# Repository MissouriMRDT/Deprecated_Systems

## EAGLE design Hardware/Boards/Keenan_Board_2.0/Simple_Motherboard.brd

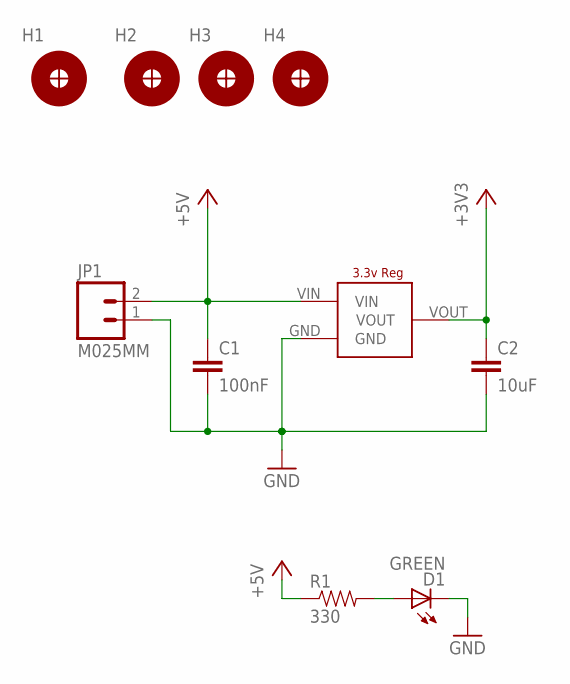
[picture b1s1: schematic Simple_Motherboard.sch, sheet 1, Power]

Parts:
C1: 100nF; 1206
C2: 10uF; 1206
D1: GREEN; LED-1206
H1, H2, H3, H4: H_MNTHOLE_#4
JP1: M025MM; SCREWTERMINAL-5MM-2
R1: 330; 1206
U$1: LD1117; LD1117SOT-223

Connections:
+3V3: C2.1, U$1.VOUT; also elsewhere on the board
+5V: C1.1, JP1.2, R1.1, U$1.VIN; also elsewhere on the board
GND: C1.2, C2.2, D1.C, JP1.1, U$1.GND; also elsewhere on the board
unnamed: D1.A, R1.2

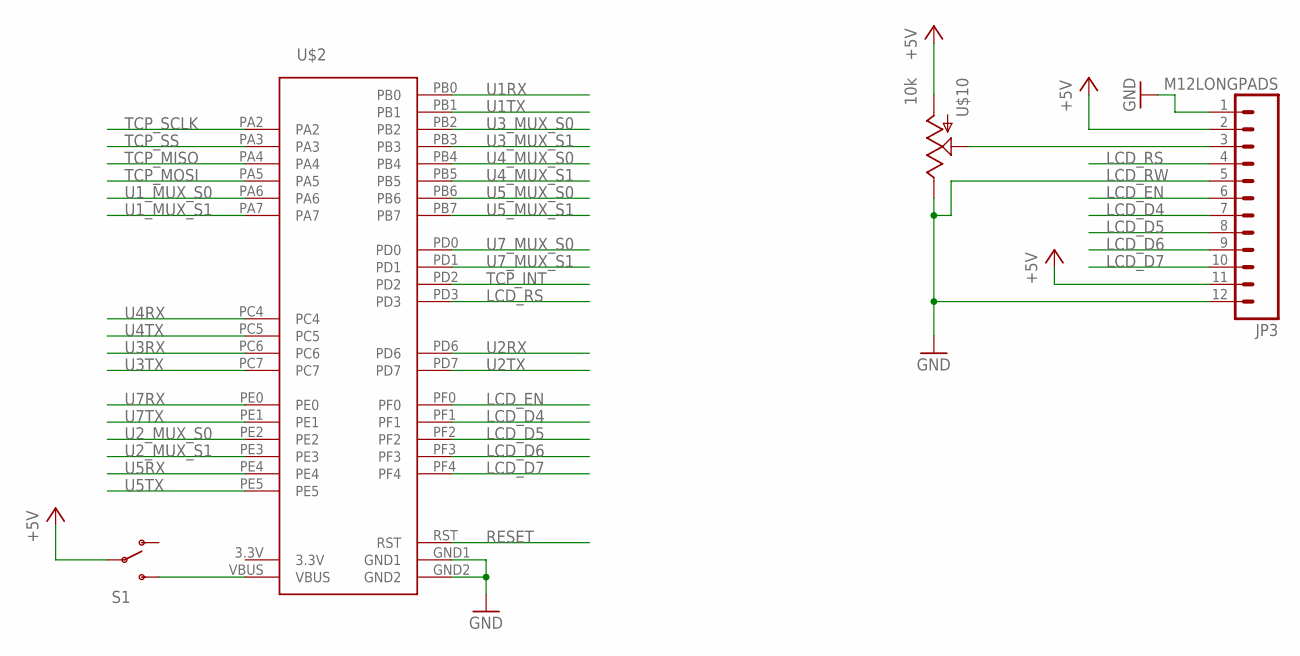
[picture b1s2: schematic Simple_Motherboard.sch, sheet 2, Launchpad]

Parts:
JP3: M12LONGPADS; 1X12_LONGPADS
S1: SWITCH-SPDTPTH_LOCK; SWITCH-SPDT_LOCK.007S
U$2: STELLARIS-LAUNCHPADSTELLARIS-LAUNCHPAD-XL; LAUNCHPAD-XL
U$10: 10k; 3362U

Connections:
3.3V: U$2.3.3V
+5V: JP3.2, JP3.11, S1.2, U$10.P$3 (A); also elsewhere on the board
GND: JP3.1, U$2.GND1, U$2.GND2; also elsewhere on the board
LCD_D4: JP3.7, U$2.PF1
LCD_D5: JP3.8, U$2.PF2
LCD_D6: JP3.9, U$2.PF3
LCD_D7: JP3.10, U$2.PF4
LCD_EN: JP3.6, U$2.PF0
LCD_RS: JP3.4, U$2.PD3
LCD_RW: JP3.5, JP3.12, U$10.P$1 (E)
unnamed: S1.3 (S), U$2.VBUS
unnamed: JP3.3, U$10.P$2 (S)
RESET: U$2.RST; also elsewhere on the board
TCP_INT: U$2.PD2; also elsewhere on the board
TCP_MISO: U$2.PA4; also elsewhere on the board
TCP_MOSI: U$2.PA5; also elsewhere on the board
TCP_SCLK: U$2.PA2; also elsewhere on the board
TCP_SS: U$2.PA3; also elsewhere on the board
U1RX: U$2.PB0; also elsewhere on the board
U1TX: U$2.PB1; also elsewhere on the board
U1_MUX_S0: U$2.PA6; also elsewhere on the board
U1_MUX_S1: U$2.PA7; also elsewhere on the board
U2RX: U$2.PD6; also elsewhere on the board
U2TX: U$2.PD7; also elsewhere on the board
U2_MUX_S0: U$2.PE2; also elsewhere on the board
U2_MUX_S1: U$2.PE3; also elsewhere on the board
U3RX: U$2.PC6; also elsewhere on the board
U3TX: U$2.PC7; also elsewhere on the board
U3_MUX_S0: U$2.PB2; also elsewhere on the board
U3_MUX_S1: U$2.PB3; also elsewhere on the board
U4RX: U$2.PC4; also elsewhere on the board
U4TX: U$2.PC5; also elsewhere on the board
U4_MUX_S0: U$2.PB4; also elsewhere on the board
U4_MUX_S1: U$2.PB5; also elsewhere on the board
U5RX: U$2.PE4; also elsewhere on the board
U5TX: U$2.PE5; also elsewhere on the board
U5_MUX_S0: U$2.PB6; also elsewhere on the board
U5_MUX_S1: U$2.PB7; also elsewhere on the board
U7RX: U$2.PE0; also elsewhere on the board
U7TX: U$2.PE1; also elsewhere on the board
U7_MUX_S0: U$2.PD0; also elsewhere on the board
U7_MUX_S1: U$2.PD1; also elsewhere on the board

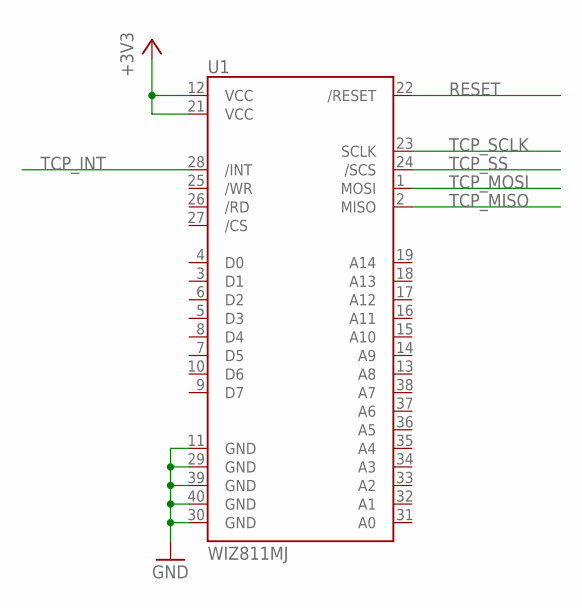
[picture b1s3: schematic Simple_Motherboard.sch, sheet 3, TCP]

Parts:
U1: WIZ811MJ

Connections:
+3V3: U1.12 (VCC), U1.21 (VCC); also elsewhere on the board
GND: U1.11 (GND), U1.29 (GND), U1.30 (GND), U1.39 (GND), U1.40 (GND); also elsewhere on the board
RESET: U1.22 (/RESET); also elsewhere on the board
TCP_INT: U1.28 (/INT); also elsewhere on the board
TCP_MISO: U1.2 (MISO); also elsewhere on the board
TCP_MOSI: U1.1 (MOSI); also elsewhere on the board
TCP_SCLK: U1.23 (SCLK); also elsewhere on the board
TCP_SS: U1.24 (/SCS); also elsewhere on the board

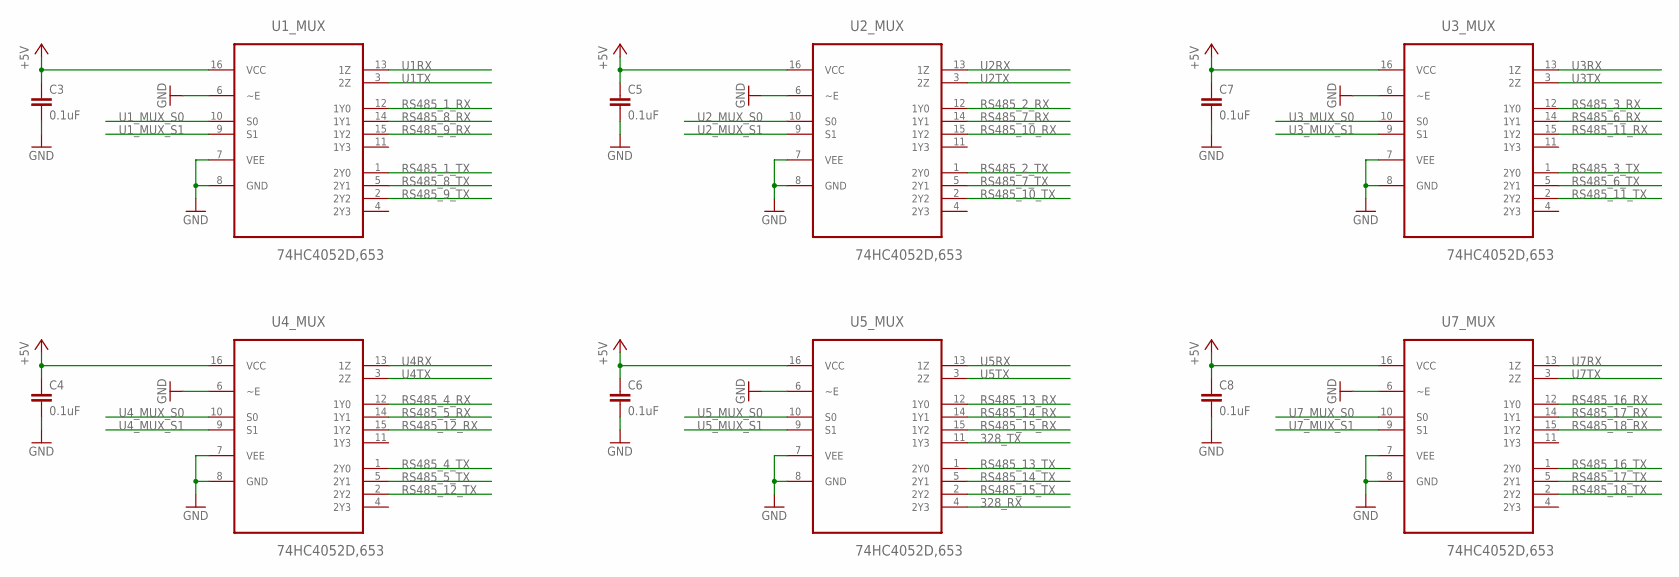
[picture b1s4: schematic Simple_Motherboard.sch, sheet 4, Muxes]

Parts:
C3, C4, C5, C6, C7, C8: 0.1uF; 1206
U1_MUX, U2_MUX, U3_MUX, U4_MUX, U5_MUX, U7_MUX: 74HC4052D,653; SOIC127P600X175-16N

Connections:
328_RX: U5_MUX.4 (2Y3); also elsewhere on the board
328_TX: U5_MUX.11 (1Y3); also elsewhere on the board
+5V: C3.1, C4.1, C5.1, C6.1, C7.1, C8.1, U1_MUX.16 (VCC), U2_MUX.16 (VCC), U3_MUX.16 (VCC), U4_MUX.16 (VCC), U5_MUX.16 (VCC), U7_MUX.16 (VCC); also elsewhere on the board
GND: C3.2, C4.2, C5.2, C6.2, C7.2, C8.2, U1_MUX.6 (~E), U1_MUX.7 (VEE), U1_MUX.8 (GND), U2_MUX.6 (~E), U2_MUX.7 (VEE), U2_MUX.8 (GND), U3_MUX.6 (~E), U3_MUX.7 (VEE), U3_MUX.8 (GND), U4_MUX.6 (~E), U4_MUX.7 (VEE), U4_MUX.8 (GND), U5_MUX.6 (~E), U5_MUX.7 (VEE), U5_MUX.8 (GND), U7_MUX.6 (~E), U7_MUX.7 (VEE), U7_MUX.8 (GND); also elsewhere on the board
RS485_1_RX: U1_MUX.12 (1Y0); also elsewhere on the board
RS485_1_TX: U1_MUX.1 (2Y0); also elsewhere on the board
RS485_2_RX: U2_MUX.12 (1Y0); also elsewhere on the board
RS485_2_TX: U2_MUX.1 (2Y0); also elsewhere on the board
RS485_3_RX: U3_MUX.12 (1Y0); also elsewhere on the board
RS485_3_TX: U3_MUX.1 (2Y0); also elsewhere on the board
RS485_4_RX: U4_MUX.12 (1Y0); also elsewhere on the board
RS485_4_TX: U4_MUX.1 (2Y0); also elsewhere on the board
RS485_5_RX: U4_MUX.14 (1Y1); also elsewhere on the board
RS485_5_TX: U4_MUX.5 (2Y1); also elsewhere on the board
RS485_6_RX: U3_MUX.14 (1Y1); also elsewhere on the board
RS485_6_TX: U3_MUX.5 (2Y1); also elsewhere on the board
RS485_7_RX: U2_MUX.14 (1Y1); also elsewhere on the board
RS485_7_TX: U2_MUX.5 (2Y1); also elsewhere on the board
RS485_8_RX: U1_MUX.14 (1Y1); also elsewhere on the board
RS485_8_TX: U1_MUX.5 (2Y1); also elsewhere on the board
RS485_9_RX: U1_MUX.15 (1Y2); also elsewhere on the board
RS485_9_TX: U1_MUX.2 (2Y2); also elsewhere on the board
RS485_10_RX: U2_MUX.15 (1Y2); also elsewhere on the board
RS485_10_TX: U2_MUX.2 (2Y2); also elsewhere on the board
RS485_11_RX: U3_MUX.15 (1Y2); also elsewhere on the board
RS485_11_TX: U3_MUX.2 (2Y2); also elsewhere on the board
RS485_12_RX: U4_MUX.15 (1Y2); also elsewhere on the board
RS485_12_TX: U4_MUX.2 (2Y2); also elsewhere on the board
RS485_13_RX: U5_MUX.12 (1Y0); also elsewhere on the board
RS485_13_TX: U5_MUX.1 (2Y0); also elsewhere on the board
RS485_14_RX: U5_MUX.14 (1Y1); also elsewhere on the board
RS485_14_TX: U5_MUX.5 (2Y1); also elsewhere on the board
RS485_15_RX: U5_MUX.15 (1Y2); also elsewhere on the board
RS485_15_TX: U5_MUX.2 (2Y2); also elsewhere on the board
RS485_16_RX: U7_MUX.12 (1Y0); also elsewhere on the board
RS485_16_TX: U7_MUX.1 (2Y0); also elsewhere on the board
RS485_17_RX: U7_MUX.14 (1Y1); also elsewhere on the board
RS485_17_TX: U7_MUX.5 (2Y1); also elsewhere on the board
RS485_18_RX: U7_MUX.15 (1Y2); also elsewhere on the board
RS485_18_TX: U7_MUX.2 (2Y2); also elsewhere on the board
U1RX: U1_MUX.13 (1Z); also elsewhere on the board
U1TX: U1_MUX.3 (2Z); also elsewhere on the board
U1_MUX_S0: U1_MUX.10 (S0); also elsewhere on the board
U1_MUX_S1: U1_MUX.9 (S1); also elsewhere on the board
U2RX: U2_MUX.13 (1Z); also elsewhere on the board
U2TX: U2_MUX.3 (2Z); also elsewhere on the board
U2_MUX_S0: U2_MUX.10 (S0); also elsewhere on the board
U2_MUX_S1: U2_MUX.9 (S1); also elsewhere on the board
U3RX: U3_MUX.13 (1Z); also elsewhere on the board
U3TX: U3_MUX.3 (2Z); also elsewhere on the board
U3_MUX_S0: U3_MUX.10 (S0); also elsewhere on the board
U3_MUX_S1: U3_MUX.9 (S1); also elsewhere on the board
U4RX: U4_MUX.13 (1Z); also elsewhere on the board
U4TX: U4_MUX.3 (2Z); also elsewhere on the board
U4_MUX_S0: U4_MUX.10 (S0); also elsewhere on the board
U4_MUX_S1: U4_MUX.9 (S1); also elsewhere on the board
U5RX: U5_MUX.13 (1Z); also elsewhere on the board
U5TX: U5_MUX.3 (2Z); also elsewhere on the board
U5_MUX_S0: U5_MUX.10 (S0); also elsewhere on the board
U5_MUX_S1: U5_MUX.9 (S1); also elsewhere on the board
U7RX: U7_MUX.13 (1Z); also elsewhere on the board
U7TX: U7_MUX.3 (2Z); also elsewhere on the board
U7_MUX_S0: U7_MUX.10 (S0); also elsewhere on the board
U7_MUX_S1: U7_MUX.9 (S1); also elsewhere on the board

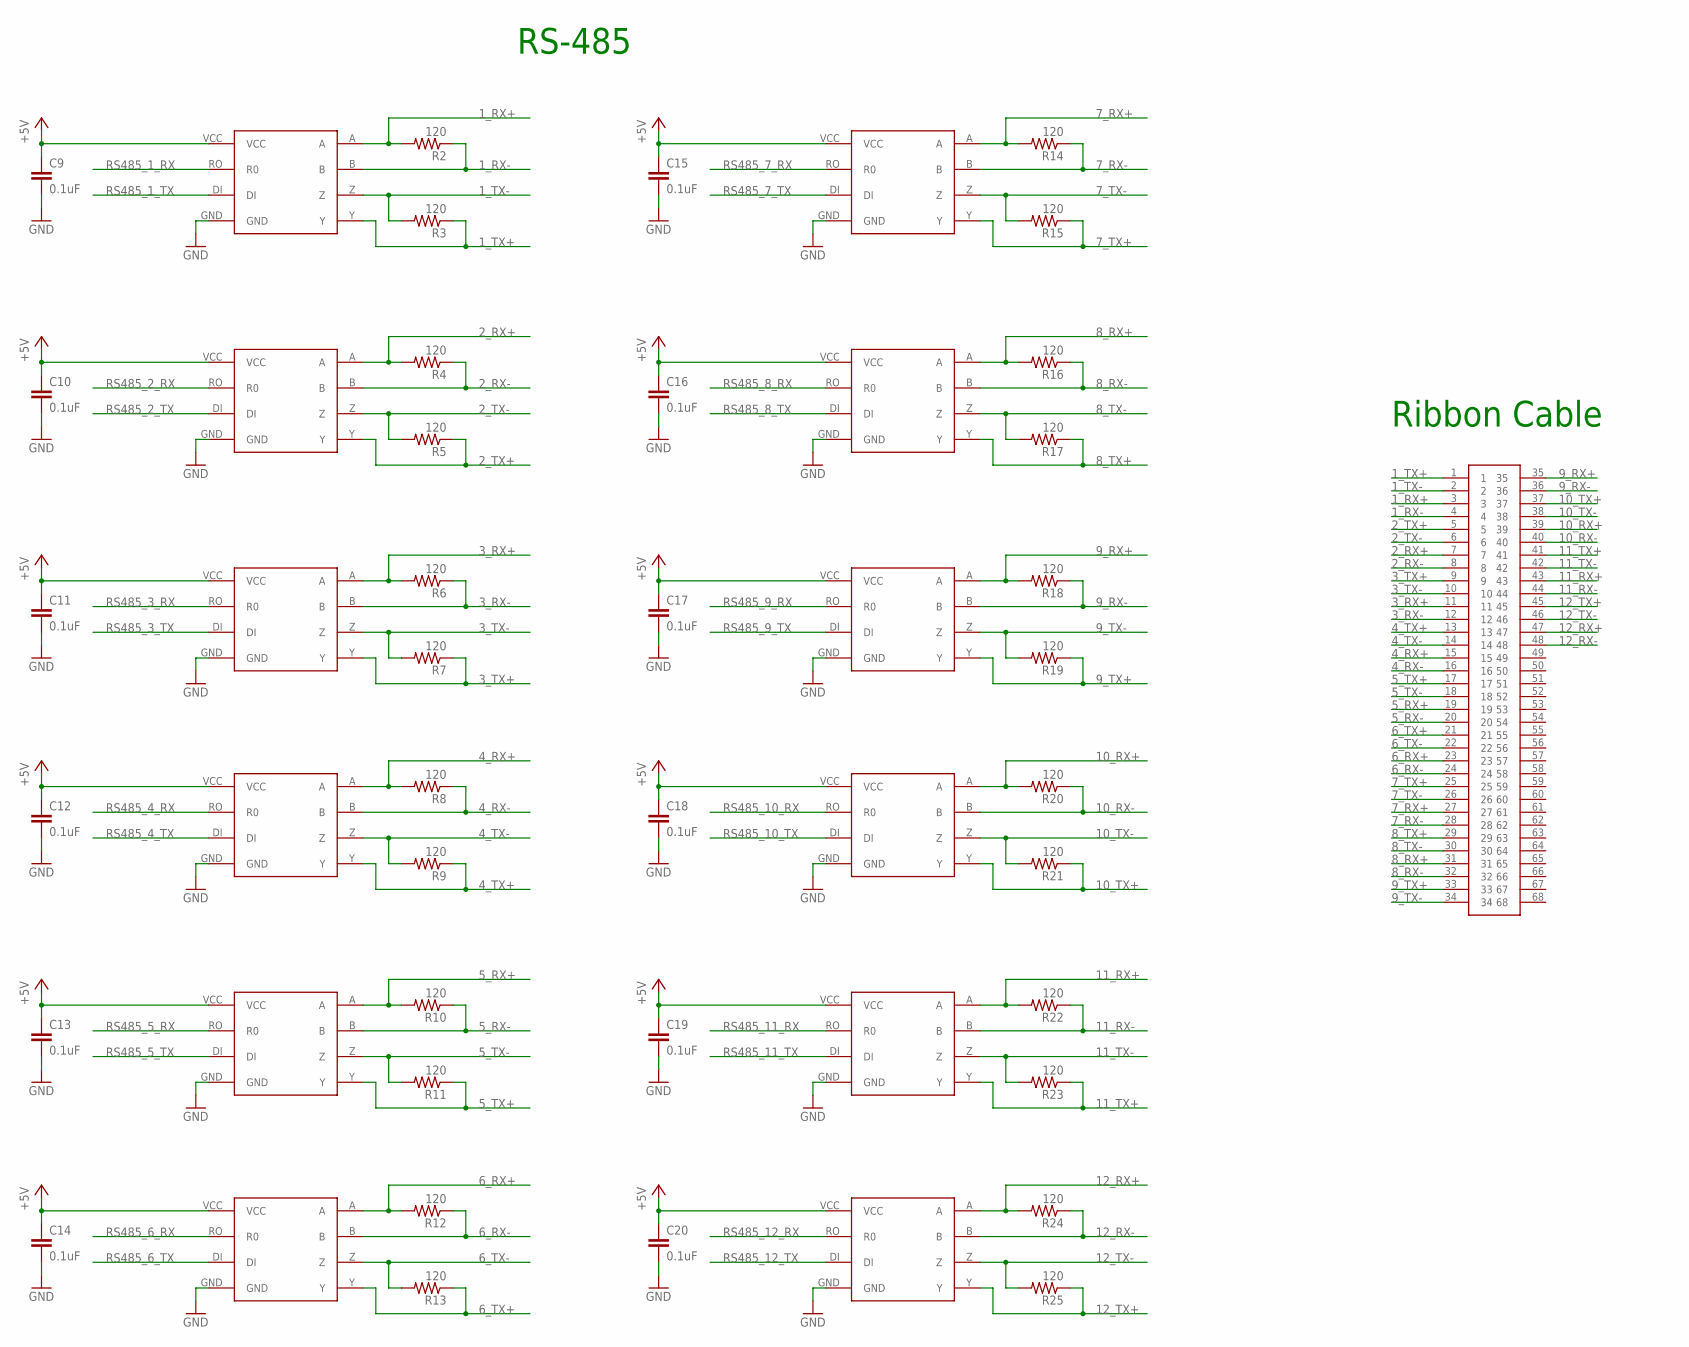
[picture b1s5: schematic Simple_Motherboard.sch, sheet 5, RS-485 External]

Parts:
C9, C10, C11, C12, C13, C14, C15, C16, C17, C18, C19, C20: 0.1uF; 1206
R2, R3, R4, R5, R6, R7, R8, R9, R10, R11, R12, R13, R14, R15, R16, R17, R18, R19, R20, R21, R22, R23, R24, R25: 120; 1206
RS_TRANS_1, RS_TRANS_2, RS_TRANS_3, RS_TRANS_4, RS_TRANS_5, RS_TRANS_6, RS_TRANS_7, RS_TRANS_8, RS_TRANS_9, RS_TRANS_10, RS_TRANS_11, RS_TRANS_12: MAX3077; MAX3070E
U$3: TB60050685100; 60050685100

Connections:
1_RX+: R2.2, RS_TRANS_1.A, U$3.3
1_RX-: R2.1, RS_TRANS_1.B, U$3.4
1_TX+: R3.1, RS_TRANS_1.Y, U$3.1
1_TX-: R3.2, RS_TRANS_1.Z, U$3.2
2_RX+: R4.2, RS_TRANS_2.A, U$3.7
2_RX-: R4.1, RS_TRANS_2.B, U$3.8
2_TX+: R5.1, RS_TRANS_2.Y, U$3.5
2_TX-: R5.2, RS_TRANS_2.Z, U$3.6
3_RX+: R6.2, RS_TRANS_3.A, U$3.11
3_RX-: R6.1, RS_TRANS_3.B, U$3.12
3_TX+: R7.1, RS_TRANS_3.Y, U$3.9
3_TX-: R7.2, RS_TRANS_3.Z, U$3.10
4_RX+: R8.2, RS_TRANS_4.A, U$3.15
4_RX-: R8.1, RS_TRANS_4.B, U$3.16
4_TX+: R9.1, RS_TRANS_4.Y, U$3.13
4_TX-: R9.2, RS_TRANS_4.Z, U$3.14
5_RX+: R10.2, RS_TRANS_5.A, U$3.19
5_RX-: R10.1, RS_TRANS_5.B, U$3.20
5_TX+: R11.1, RS_TRANS_5.Y, U$3.17
5_TX-: R11.2, RS_TRANS_5.Z, U$3.18
6_RX+: R12.2, RS_TRANS_6.A, U$3.23
6_RX-: R12.1, RS_TRANS_6.B, U$3.24
6_TX+: R13.1, RS_TRANS_6.Y, U$3.21
6_TX-: R13.2, RS_TRANS_6.Z, U$3.22
7_RX+: R14.2, RS_TRANS_7.A, U$3.27
7_RX-: R14.1, RS_TRANS_7.B, U$3.28
7_TX+: R15.1, RS_TRANS_7.Y, U$3.25
7_TX-: R15.2, RS_TRANS_7.Z, U$3.26
8_RX+: R16.2, RS_TRANS_8.A, U$3.31
8_RX-: R16.1, RS_TRANS_8.B, U$3.32
8_TX+: R17.1, RS_TRANS_8.Y, U$3.29
8_TX-: R17.2, RS_TRANS_8.Z, U$3.30
9_RX+: R18.2, RS_TRANS_9.A, U$3.35
9_RX-: R18.1, RS_TRANS_9.B, U$3.36
9_TX+: R19.1, RS_TRANS_9.Y, U$3.33
9_TX-: R19.2, RS_TRANS_9.Z, U$3.34
10_RX+: R20.2, RS_TRANS_10.A, U$3.39
10_RX-: R20.1, RS_TRANS_10.B, U$3.40
10_TX+: R21.1, RS_TRANS_10.Y, U$3.37
10_TX-: R21.2, RS_TRANS_10.Z, U$3.38
11_RX+: R22.2, RS_TRANS_11.A, U$3.43
11_RX-: R22.1, RS_TRANS_11.B, U$3.44
11_TX+: R23.1, RS_TRANS_11.Y, U$3.41
11_TX-: R23.2, RS_TRANS_11.Z, U$3.42
12_RX+: R24.2, RS_TRANS_12.A, U$3.47
12_RX-: R24.1, RS_TRANS_12.B, U$3.48
12_TX+: R25.1, RS_TRANS_12.Y, U$3.45
12_TX-: R25.2, RS_TRANS_12.Z, U$3.46
+5V: C9.1, C10.1, C11.1, C12.1, C13.1, C14.1, C15.1, C16.1, C17.1, C18.1, C19.1, C20.1, RS_TRANS_1.VCC, RS_TRANS_2.VCC, RS_TRANS_3.VCC, RS_TRANS_4.VCC, RS_TRANS_5.VCC, RS_TRANS_6.VCC, RS_TRANS_7.VCC, RS_TRANS_8.VCC, RS_TRANS_9.VCC, RS_TRANS_10.VCC, RS_TRANS_11.VCC, RS_TRANS_12.VCC; also elsewhere on the board
GND: C9.2, C10.2, C11.2, C12.2, C13.2, C14.2, C15.2, C16.2, C17.2, C18.2, C19.2, C20.2, RS_TRANS_1.GND, RS_TRANS_2.GND, RS_TRANS_3.GND, RS_TRANS_4.GND, RS_TRANS_5.GND, RS_TRANS_6.GND, RS_TRANS_7.GND, RS_TRANS_8.GND, RS_TRANS_9.GND, RS_TRANS_10.GND, RS_TRANS_11.GND, RS_TRANS_12.GND; also elsewhere on the board
RS485_1_RX: RS_TRANS_1.RO (R0); also elsewhere on the board
RS485_1_TX: RS_TRANS_1.DI; also elsewhere on the board
RS485_2_RX: RS_TRANS_2.RO (R0); also elsewhere on the board
RS485_2_TX: RS_TRANS_2.DI; also elsewhere on the board
RS485_3_RX: RS_TRANS_3.RO (R0); also elsewhere on the board
RS485_3_TX: RS_TRANS_3.DI; also elsewhere on the board
RS485_4_RX: RS_TRANS_4.RO (R0); also elsewhere on the board
RS485_4_TX: RS_TRANS_4.DI; also elsewhere on the board
RS485_5_RX: RS_TRANS_5.RO (R0); also elsewhere on the board
RS485_5_TX: RS_TRANS_5.DI; also elsewhere on the board
RS485_6_RX: RS_TRANS_6.RO (R0); also elsewhere on the board
RS485_6_TX: RS_TRANS_6.DI; also elsewhere on the board
RS485_7_RX: RS_TRANS_7.RO (R0); also elsewhere on the board
RS485_7_TX: RS_TRANS_7.DI; also elsewhere on the board
RS485_8_RX: RS_TRANS_8.RO (R0); also elsewhere on the board
RS485_8_TX: RS_TRANS_8.DI; also elsewhere on the board
RS485_9_RX: RS_TRANS_9.RO (R0); also elsewhere on the board
RS485_9_TX: RS_TRANS_9.DI; also elsewhere on the board
RS485_10_RX: RS_TRANS_10.RO (R0); also elsewhere on the board
RS485_10_TX: RS_TRANS_10.DI; also elsewhere on the board
RS485_11_RX: RS_TRANS_11.RO (R0); also elsewhere on the board
RS485_11_TX: RS_TRANS_11.DI; also elsewhere on the board
RS485_12_RX: RS_TRANS_12.RO (R0); also elsewhere on the board
RS485_12_TX: RS_TRANS_12.DI; also elsewhere on the board

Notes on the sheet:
Ribbon Cable
RS-485

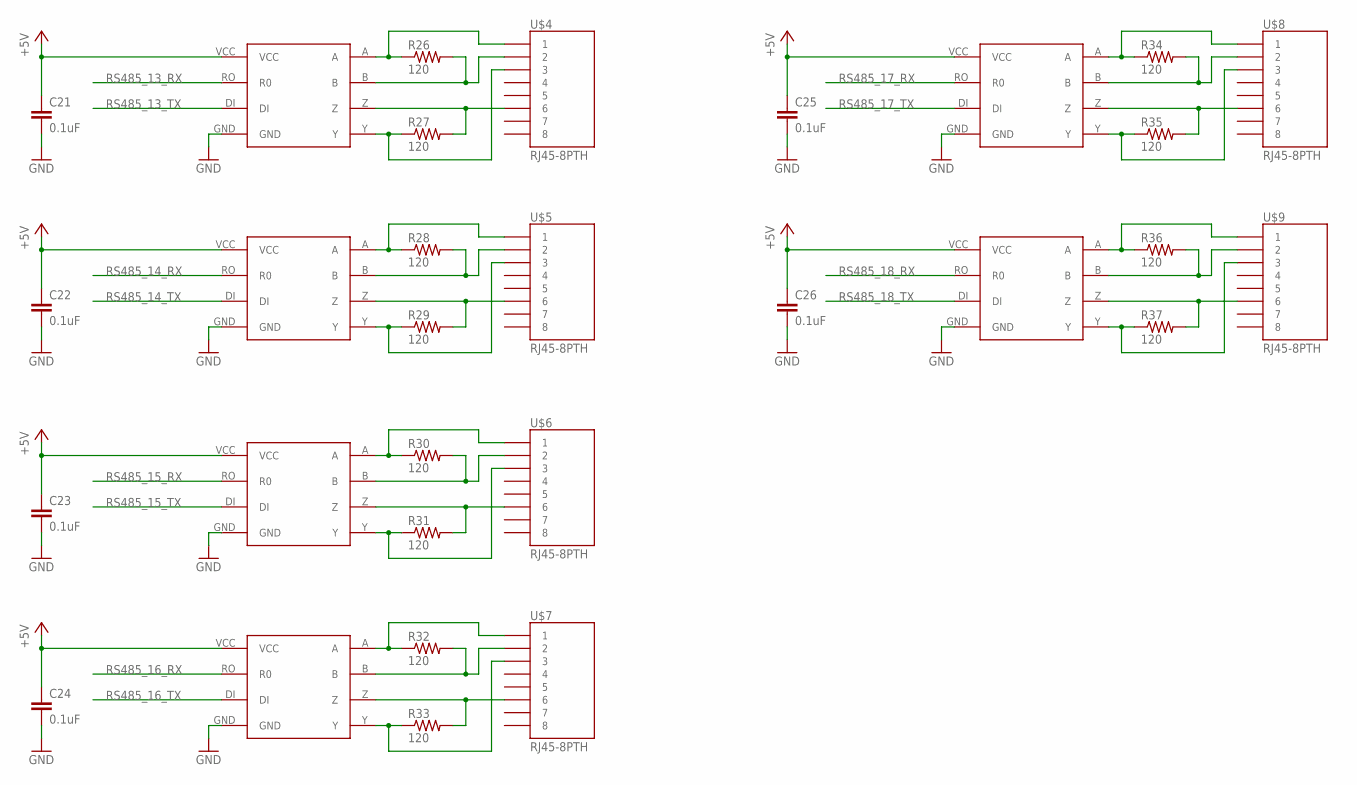
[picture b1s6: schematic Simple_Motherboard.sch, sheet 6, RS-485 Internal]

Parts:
C21, C22, C23, C24, C25, C26: 0.1uF; 1206
R26, R27, R28, R29, R30, R31, R32, R33, R34, R35, R36, R37: 120; 1206
RS-485-1, RS-485-2, RS-485-3, RS-485-4, RS-485-5, RS-485-6: MAX3077; MAX3070E
U$4, U$5, U$6, U$7, U$8, U$9: RJ45-8PTH; RJ45-8

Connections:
+5V: C21.1, C22.1, C23.1, C24.1, C25.1, C26.1, RS-485-1.VCC, RS-485-2.VCC, RS-485-3.VCC, RS-485-4.VCC, RS-485-5.VCC, RS-485-6.VCC; also elsewhere on the board
GND: C21.2, C22.2, C23.2, C24.2, C25.2, C26.2, RS-485-1.GND, RS-485-2.GND, RS-485-3.GND, RS-485-4.GND, RS-485-5.GND, RS-485-6.GND; also elsewhere on the board
unnamed: R26.1, RS-485-1.A, U$4.1
unnamed: R26.2, RS-485-1.B, U$4.2
unnamed: R27.1, RS-485-1.Y, U$4.3
unnamed: R29.2, RS-485-2.Z, U$5.6
unnamed: R27.2, RS-485-1.Z, U$4.6
unnamed: R28.1, RS-485-2.A, U$5.1
unnamed: R28.2, RS-485-2.B, U$5.2
unnamed: R29.1, RS-485-2.Y, U$5.3
unnamed: R31.2, RS-485-3.Z, U$6.6
unnamed: R30.1, RS-485-3.A, U$6.1
unnamed: R30.2, RS-485-3.B, U$6.2
unnamed: R31.1, RS-485-3.Y, U$6.3
unnamed: R33.2, RS-485-4.Z, U$7.6
unnamed: R32.1, RS-485-4.A, U$7.1
unnamed: R32.2, RS-485-4.B, U$7.2
unnamed: R33.1, RS-485-4.Y, U$7.3
unnamed: R35.2, RS-485-5.Z, U$8.6
unnamed: R34.1, RS-485-5.A, U$8.1
unnamed: R34.2, RS-485-5.B, U$8.2
unnamed: R35.1, RS-485-5.Y, U$8.3
unnamed: R37.2, RS-485-6.Z, U$9.6
unnamed: R36.1, RS-485-6.A, U$9.1
unnamed: R36.2, RS-485-6.B, U$9.2
unnamed: R37.1, RS-485-6.Y, U$9.3
RS485_13_RX: RS-485-1.RO (R0); also elsewhere on the board
RS485_13_TX: RS-485-1.DI; also elsewhere on the board
RS485_14_RX: RS-485-2.RO (R0); also elsewhere on the board
RS485_14_TX: RS-485-2.DI; also elsewhere on the board
RS485_15_RX: RS-485-3.RO (R0); also elsewhere on the board
RS485_15_TX: RS-485-3.DI; also elsewhere on the board
RS485_16_RX: RS-485-4.RO (R0); also elsewhere on the board
RS485_16_TX: RS-485-4.DI; also elsewhere on the board
RS485_17_RX: RS-485-5.RO (R0); also elsewhere on the board
RS485_17_TX: RS-485-5.DI; also elsewhere on the board
RS485_18_RX: RS-485-6.RO (R0); also elsewhere on the board
RS485_18_TX: RS-485-6.DI; also elsewhere on the board

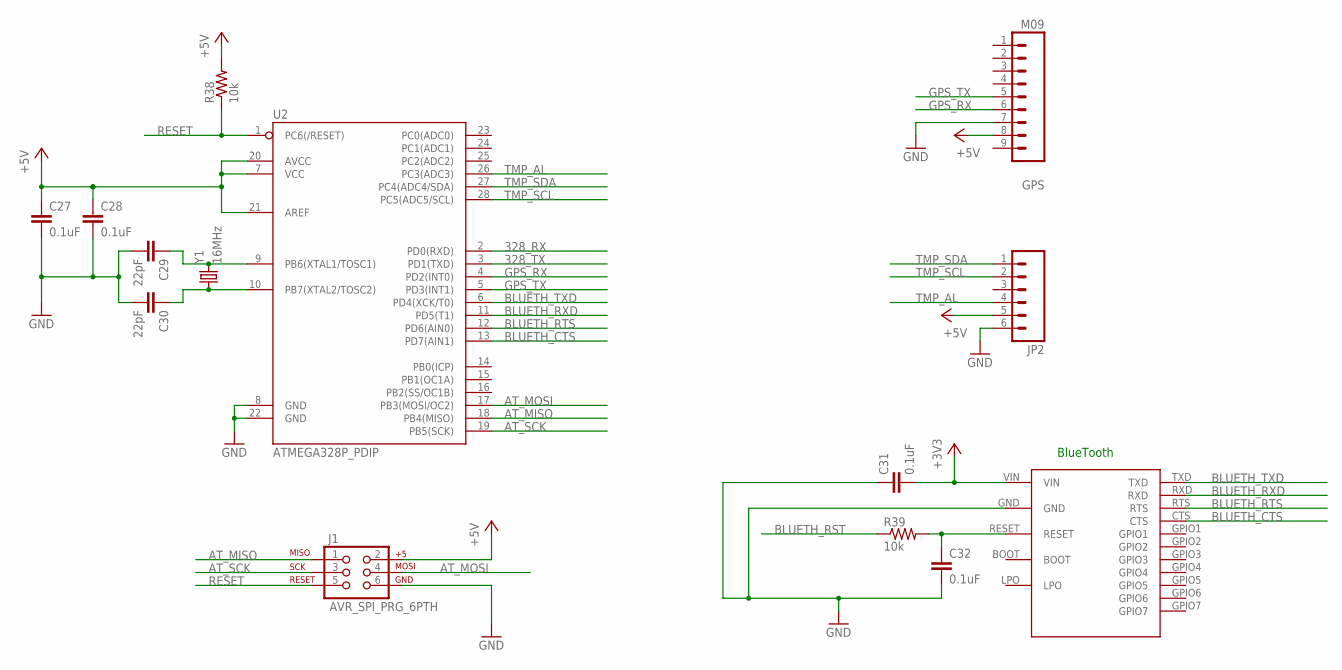
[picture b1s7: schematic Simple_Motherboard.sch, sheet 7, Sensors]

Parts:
BLUETOOTH: SPBT2632C2A
C27, C28, C31, C32: 0.1uF; 1206
C29, C30: 22pF; 1206
GPS: M09; 1X09
J1: AVR_SPI_PRG_6PTH; 2X3
JP2: M06LONGPADS; 1X06_LONGPADS
R38, R39: 10k; 1206
U2: ATMEGA328P_PDIP; DIL28-3
Y1: 16MHz; HC49US

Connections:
328_RX: U2.2 (PD0(RXD)); also elsewhere on the board
328_TX: U2.3 (PD1(TXD)); also elsewhere on the board
+3V3: BLUETOOTH.VIN, C31.2; also elsewhere on the board
+5V: C27.1, C28.1, GPS.8, J1.2, JP2.5, R38.2, U2.7 (VCC), U2.20 (AVCC), U2.21 (AREF); also elsewhere on the board
ATCLK3: C30.1, U2.10 (PB7(XTAL2/TOSC2)), Y1.1
ATCLK4: C29.1, U2.9 (PB6(XTAL1/TOSC1)), Y1.2
AT_MISO: J1.1, U2.18 (PB4(MISO))
AT_MOSI: J1.4, U2.17 (PB3(MOSI/OC2))
AT_SCK: J1.3, U2.19 (PB5(SCK))
BLUETH_CTS: BLUETOOTH.CTS, U2.13 (PD7(AIN1))
BLUETH_RST: R39.1
BLUETH_RTS: BLUETOOTH.RTS, U2.12 (PD6(AIN0))
BLUETH_RXD: BLUETOOTH.RXD, U2.11 (PD5(T1))
BLUETH_TXD: BLUETOOTH.TXD, U2.6 (PD4(XCK/T0))
GND: BLUETOOTH.GND, C27.2, C28.2, C29.2, C30.2, C31.1, C32.2, GPS.7, J1.6, JP2.6, U2.8 (GND), U2.22 (GND); also elsewhere on the board
GPS_RX: GPS.6, U2.4 (PD2(INT0))
GPS_TX: GPS.5, U2.5 (PD3(INT1))
unnamed: BLUETOOTH.RESET, C32.1, R39.2
RESET: J1.5, R38.1, U2.1 (PC6(/RESET)); also elsewhere on the board
TMP_AL: JP2.4, U2.26 (PC3(ADC3))
TMP_SCL: JP2.2, U2.28 (PC5(ADC5/SCL))
TMP_SDA: JP2.1, U2.27 (PC4(ADC4/SDA))

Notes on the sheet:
BlueTooth

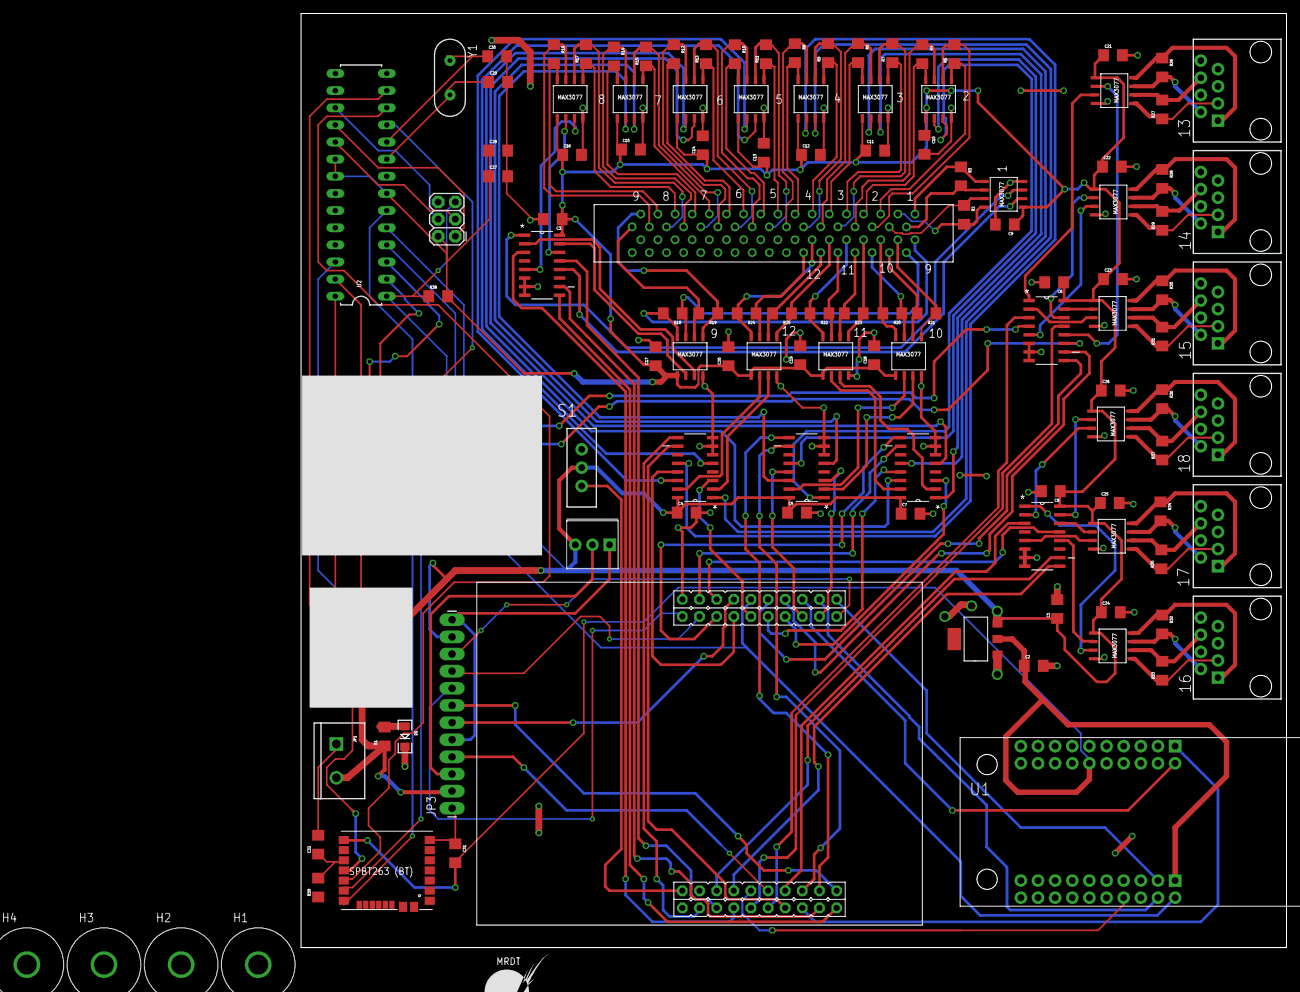
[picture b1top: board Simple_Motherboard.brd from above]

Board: 2 copper layers, 146.1 x 138.4 mm, 120 parts (0 on the bottom side), 168 nets.

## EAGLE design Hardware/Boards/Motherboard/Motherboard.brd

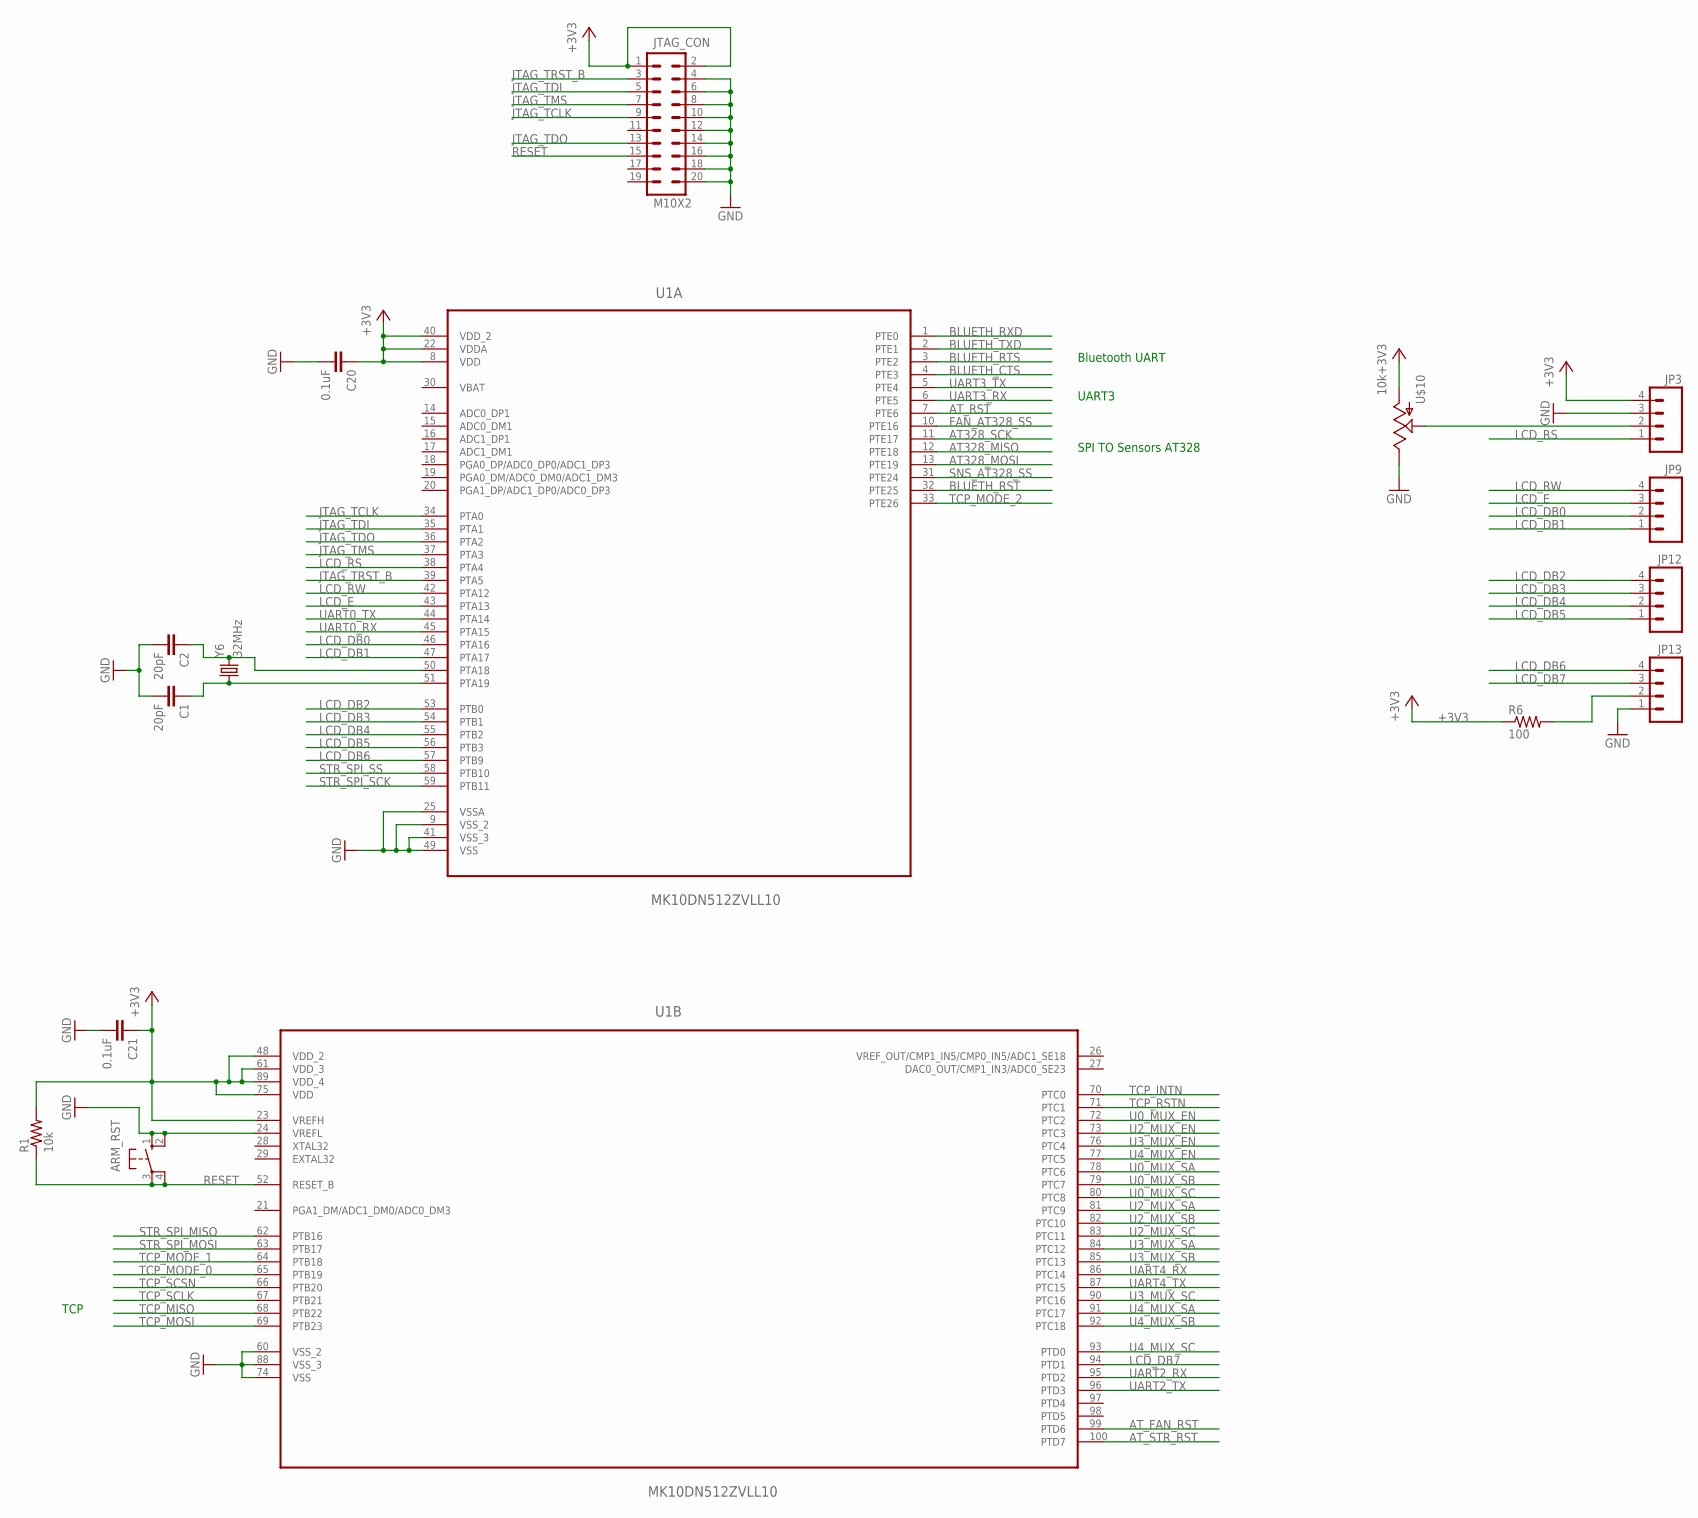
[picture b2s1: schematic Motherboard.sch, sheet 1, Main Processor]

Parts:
ARM_RST: 10-XX; B3F-10XX
C1, C2: 20pF; 1206
C20, C21: 0.1uF; 1206
JP3, JP9, JP12, JP13: M04POLAR; MOLEX-1X4
JTAG_CON: M10X2; 2X10
R1: 10k; 1206
R6: 100; 1206
U1: MK10DN512ZVLL10; QFP50P1600X1600X170-100N
U$10: 10k; 3362U
Y6: 32MHz; CRYSTAL-SMD-5X3

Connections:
+3V3: C20.1, C21.1, JP3.4, JTAG_CON.1, JTAG_CON.2, R1.2, R6.1, U1.8 (VDD), U1.22 (VDDA), U1.23 (VREFH), U1.40 (VDD_2), U1.48 (VDD_2), U1.61 (VDD_3), U1.75 (VDD), U1.89 (VDD_4), U$10.P$3 (A); also elsewhere on the board
AT328_MISO: U1.12 (PTE18); also elsewhere on the board
AT328_MOSI: U1.13 (PTE19); also elsewhere on the board
AT328_SCK: U1.11 (PTE17); also elsewhere on the board
AT_FAN_RST: U1.99 (PTD6); also elsewhere on the board
AT_RST: U1.7 (PTE6); also elsewhere on the board
AT_STR_RST: U1.100 (PTD7); also elsewhere on the board
BLUETH_CTS: U1.4 (PTE3); also elsewhere on the board
BLUETH_RST: U1.32 (PTE25); also elsewhere on the board
BLUETH_RTS: U1.3 (PTE2); also elsewhere on the board
BLUETH_RXD: U1.1 (PTE0); also elsewhere on the board
BLUETH_TXD: U1.2 (PTE1); also elsewhere on the board
CLKI: C2.1, U1.50 (PTA18), Y6.3 (2)
CLKO: C1.1, U1.51 (PTA19), Y6.1
FAN_AT328_SS: U1.10 (PTE16); also elsewhere on the board
GND: ARM_RST.1 (S), ARM_RST.2 (S1), C1.2, C2.2, C20.2, C21.2, JP3.3, JP13.1, JTAG_CON.4, JTAG_CON.6, JTAG_CON.8, JTAG_CON.10, JTAG_CON.12, JTAG_CON.14, JTAG_CON.16, JTAG_CON.18, JTAG_CON.20, U1.9 (VSS_2), U1.24 (VREFL), U1.25 (VSSA), U1.41 (VSS_3), U1.49 (VSS), U1.60 (VSS_2), U1.74 (VSS), U1.88 (VSS_3), U$10.P$1 (E); also elsewhere on the board
JTAG_TCLK: JTAG_CON.9, U1.34 (PTA0)
JTAG_TDI: JTAG_CON.5, U1.35 (PTA1)
JTAG_TDO: JTAG_CON.13, U1.36 (PTA2)
JTAG_TMS: JTAG_CON.7, U1.37 (PTA3)
JTAG_TRST_B: JTAG_CON.3, U1.39 (PTA5)
LCD_DB0: JP9.2, U1.46 (PTA16)
LCD_DB1: JP9.1, U1.47 (PTA17)
LCD_DB2: JP12.4, U1.53 (PTB0)
LCD_DB3: JP12.3, U1.54 (PTB1)
LCD_DB4: JP12.2, U1.55 (PTB2)
LCD_DB5: JP12.1, U1.56 (PTB3)
LCD_DB6: JP13.4, U1.57 (PTB9)
LCD_DB7: JP13.3, U1.94 (PTD1)
LCD_E: JP9.3, U1.43 (PTA13)
LCD_RS: JP3.1, U1.38 (PTA4)
LCD_RW: JP9.4, U1.42 (PTA12)
unnamed: JP13.2, R6.2
unnamed: JP3.2, U$10.P$2 (S)
RESET: ARM_RST.3, ARM_RST.4 (P1), JTAG_CON.15, R1.1, U1.52 (RESET_B)
SNS_AT328_SS: U1.31 (PTE24); also elsewhere on the board
STR_SPI_MISO: U1.62 (PTB16); also elsewhere on the board
STR_SPI_MOSI: U1.63 (PTB17); also elsewhere on the board
STR_SPI_SCK: U1.59 (PTB11); also elsewhere on the board
STR_SPI_SS: U1.58 (PTB10); also elsewhere on the board
TCP_INTN: U1.70 (PTC0); also elsewhere on the board
TCP_MISO: U1.68 (PTB22); also elsewhere on the board
TCP_MODE_0: U1.65 (PTB19); also elsewhere on the board
TCP_MODE_1: U1.64 (PTB18); also elsewhere on the board
TCP_MODE_2: U1.33 (PTE26); also elsewhere on the board
TCP_MOSI: U1.69 (PTB23); also elsewhere on the board
TCP_RSTN: U1.71 (PTC1); also elsewhere on the board
TCP_SCLK: U1.67 (PTB21); also elsewhere on the board
TCP_SCSN: U1.66 (PTB20); also elsewhere on the board
U0_MUX_EN: U1.72 (PTC2); also elsewhere on the board
U0_MUX_SA: U1.78 (PTC6); also elsewhere on the board
U0_MUX_SB: U1.79 (PTC7); also elsewhere on the board
U0_MUX_SC: U1.80 (PTC8); also elsewhere on the board
U2_MUX_EN: U1.73 (PTC3); also elsewhere on the board
U2_MUX_SA: U1.81 (PTC9); also elsewhere on the board
U2_MUX_SB: U1.82 (PTC10); also elsewhere on the board
U2_MUX_SC: U1.83 (PTC11); also elsewhere on the board
U3_MUX_EN: U1.76 (PTC4); also elsewhere on the board
U3_MUX_SA: U1.84 (PTC12); also elsewhere on the board
U3_MUX_SB: U1.85 (PTC13); also elsewhere on the board
U3_MUX_SC: U1.90 (PTC16); also elsewhere on the board
U4_MUX_EN: U1.77 (PTC5); also elsewhere on the board
U4_MUX_SA: U1.91 (PTC17); also elsewhere on the board
U4_MUX_SB: U1.92 (PTC18); also elsewhere on the board
U4_MUX_SC: U1.93 (PTD0); also elsewhere on the board
UART0_RX: U1.45 (PTA15); also elsewhere on the board
UART0_TX: U1.44 (PTA14); also elsewhere on the board
UART2_RX: U1.95 (PTD2); also elsewhere on the board
UART2_TX: U1.96 (PTD3); also elsewhere on the board
UART3_RX: U1.6 (PTE5); also elsewhere on the board
UART3_TX: U1.5 (PTE4); also elsewhere on the board
UART4_RX: U1.86 (PTC14); also elsewhere on the board
UART4_TX: U1.87 (PTC15); also elsewhere on the board
VBAT: U1.30 (VBAT)

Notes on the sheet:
Bluetooth UART
TCP
UART3
SPI TO Sensors AT328

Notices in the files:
parts and their libraries:
SparkFun-Connectors: Licensing: CC v3.0 Share-Alike You are welcome to use this library for commercial purposes.
SparkFun-Electromechanical: Licensing: Creative Commons ShareAlike 4.0 International - https://creativecommons.org/licenses/by-sa/4.0
